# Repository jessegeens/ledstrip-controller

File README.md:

# LED Strip Controller 

This repository contains source files for an ESP32-based LED strip controller. The PCB is designed in KiCad, and the schematics and PCB layout can be found under `hardware`. Software will become available under `software` once I've written it.

## Hardware
### Requirements

- KiCad 
- [Espressif KiCad libraries](https://github.com/espressif/kicad-libraries) (required to resolve the ESP32 symbols/footprints used in the schematic and PCB)

### Components
|Name|AliExpress link|
|----|---------------|
|ESP32-C3-DevKitM-1|[https://aliexpress.com/item/1005009148596443.html](https://aliexpress.com/item/1005009148596443.html)|
|XL1509-3.3|[https://aliexpress.com/item/1005009637375630.html](https://aliexpress.com/item/1005009637375630.html)|
|TIP120 Transistors (3x)|[https://aliexpress.com/item/1005008609164136.html](https://aliexpress.com/item/1005008609164136.html)|
|1K Resistor (3x)||
|220uF Capacitor||
|470uF Capacitor||
|68uH inductor||
|Pin headers (male)||
|Barrel Jack Connector|[https://aliexpress.com/item/4001206395694.html](https://aliexpress.com/item/4001206395694.html)|

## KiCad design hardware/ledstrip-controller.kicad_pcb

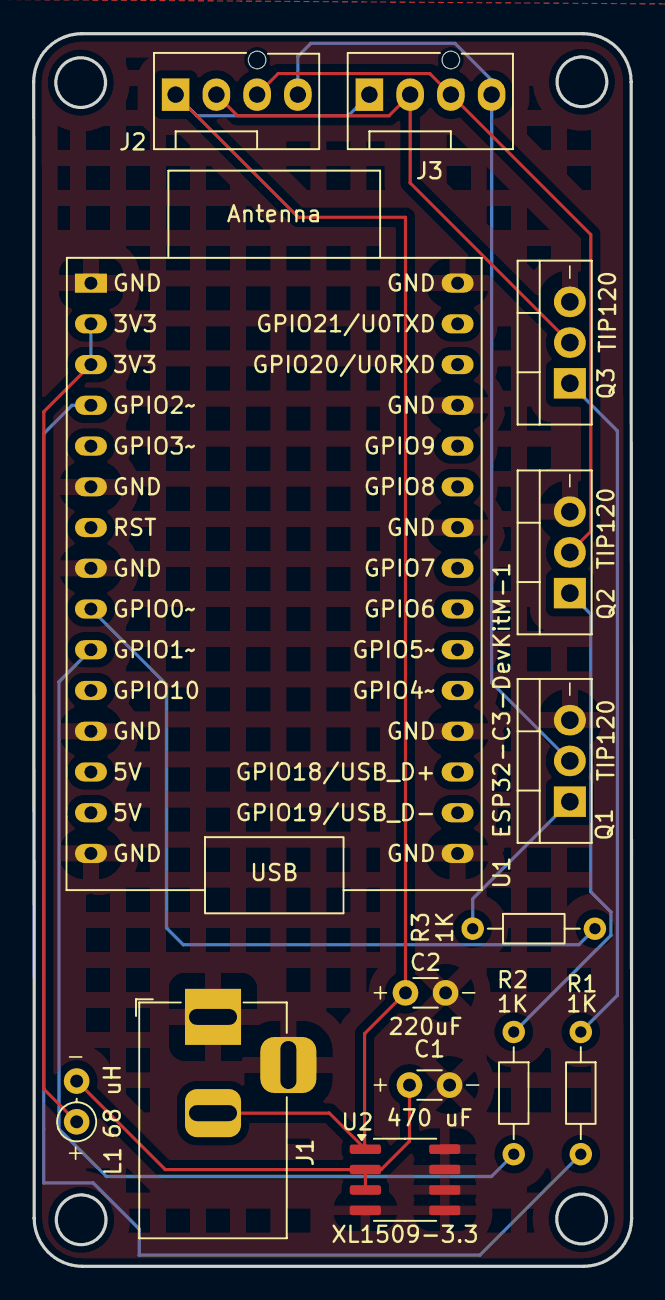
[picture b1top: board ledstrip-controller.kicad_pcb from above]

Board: 2 copper layers, 37.3 x 76.8 mm, 14 parts (0 on the bottom side), 13 nets.

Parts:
C1: 470 uF; C_Disc_D3.0mm_W1.6mm_P2.50mm
C2: 220uF; C_Disc_D3.0mm_W1.6mm_P2.50mm
J1: Barrel_Jack_Switch; BarrelJack_Horizontal
J2, J3: Conn_01x04_Pin; FanPinHeader_1x04_P2.54mm_Vertical
L1: 68 uH; L_Axial_L5.3mm_D2.2mm_P2.54mm_Vertical_Vishay_IM-1
Q1, Q2, Q3: TIP120; TO-220-3_Vertical
R1, R2, R3: 1K; R_Axial_DIN0204_L3.6mm_D1.6mm_P7.62mm_Horizontal
U1: ESP32-C3-DevKitM-1
U2: XL1509-3.3; SOIC-8_3.9x4.9mm_P1.27mm

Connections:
3V3: L1.1, U1.2 (3V3), U1.3 (3V3)
GND: C1.2, C2.2, J1.1, J1.3, Q1.3 (E), Q2.3 (E), Q3.3 (E), U1.1 (GND), U1.6 (GND), U1.8 (GND), U1.12 (GND), U1.15 (GND), U1.16 (GND), U1.19 (GND), U1.24 (GND), U1.27 (GND), U1.30 (GND), U2.4 (~EN), U2.5 (GND), U2.6 (GND), U2.7 (GND), U2.8 (GND)
unnamed: C2.1, J1.2, J2.1, J3.1, U2.1 (VIN)
unnamed: J2.2, J3.2, Q3.2 (C)
unnamed: J2.3, J3.3, Q2.2 (C)
unnamed: J2.4, J3.4, Q1.2 (C)
unnamed: Q1.1 (B), R3.1
unnamed: Q2.1 (B), R2.1
unnamed: Q3.1 (B), R1.1
unnamed: R3.2, U1.9 (GPIO0)
unnamed: R2.2, U1.10 (GPIO1)
unnamed: R1.2, U1.4 (GPIO2)
unnamed: C1.1, L1.2, U2.2 (OUT), U2.3 (FB)

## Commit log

2025-10-04 initial PCB design
